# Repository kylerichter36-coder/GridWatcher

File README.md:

# GridWatcher v0.3

> An edge electrical grid telemetry device that monitors AC line fluctuations and predicts power outages 20 to 60 seconds before they happen, sending alerts over 4G LTE cellular. Built for **Hack Club Fallen** (Maker Faire Shenzhen, Dec 2026).

**Author:** Kyle Mason Richter (`@fuelled` on Hack Club Slack / `kylerichter36-coder` on GitHub)  
**Target:** Hack Club Fallen — Maker Faire Shenzhen (Dec 11–14, 2026)  
**Hardware Repo:** [https://github.com/kylerichter36-coder/GridWatcher](https://github.com/kylerichter36-coder/GridWatcher)  
**BOM:** [bom.csv](bom.csv) (Includes links and pricing for every single part)  
**3D CAD Assembly:** [GriDwatcher_china_v0.3.step](Hardware/GridWatcher_v0.3/GriDwatcher_china_v0.3.step)  

---

## Why I Built This

If you live in South Africa like me, you already know the problem: our power grid is completely broken. Between rolling blackouts (load shedding), localized substation cable theft, and sudden breaker trips, our electricity cuts out all the time without any warning. These sudden drops corrupt computers, kill power supplies, and leave households stranded in the dark.

Most commercial energy monitors are totally reactive—they only text you *after* the power is already dead. But power grids dont just vanish instantaneously: before an electrical feeder collapses, the system exhibits measurable micro-fluctuations (sub-hertz frequency jitter, voltage sag gradients, and harmonic noise). 

I built GridWatcher to measure these exact micro-fluctuations and predict outages **20 to 60 seconds before total power failure**, giving you time to save your work, shut down sensitive equipment, or switch over backup systems.

---

## How to Use GridWatcher

GridWatcher is designed to be an autonomous, set-and-forget wall monitor:

1. **Installation & AC Hookup:**  
   Plug the device directly into an AC wall socket (100–240V AC, 50/60Hz) or wire it into your home electrical distribution board. Input power is protected by an on-board 1A slow-blow fuse and 10D471K MOV surge clamp.
2. **Autonomous Startup & 4G Link:**  
   On boot, the isolated Hi-Link 5V power supply turns on the board and starts charging the backup LiPo battery via the BQ24074 PMIC. The SIMCom A7670E modem connects to the local cellular tower over LTE Cat-1. It requires zero Wi-Fi pairing or local router dependencies, so it stays online even when home routers die during grid failures.
3. **Real-Time Monitoring:**  
   The BL0939 IC continuously measures line voltage, current, and frequency. The ESP32-S3 runs the deterministic state classifier and feeds rolling feature buffers into the Random Forest prediction engine.
4. **Early-Warning Outage Prediction:**  
   If the ML engine detects voltage sag slopes or frequency decay jitter indicating grid failure within the upcoming 20–60 seconds, it sends an immediate SMS alert and MQTT warning to your phone so you can save work and protect equipment before the blackout hits.
5. **Blackout Ride-Through & Black-Box Logging:**  
   When mains power drops, the battery circuit takes over with zero drop-out. The device freezes the preceding 60 seconds of high-speed electrical waveform data to the 1GB SD-NAND flash chip for post-incident diagnostics.

---

## 3D CAD Assembly & Physical Design

GridWatcher is designed as a monolithic 2-layer integrated PCBA (113.40 x 69.22 mm) that mounts cleanly inside a 3D-printed snap-fit wall enclosure. Zero loose devboards, zero breadboard jumper wires, and zero external USB ports that collect dust.

*Full 3D CAD STEP mechanical model available at [Hardware/GridWatcher_v0.3/GriDwatcher_china_v0.3.step](Hardware/GridWatcher_v0.3/GriDwatcher_china_v0.3.step).*

---

## How It Works (System Architecture)

```
[230V AC Mains] 
       │
       ├──> [Hi-Link HLK-10M05 5V SMPS] ──> [CLC Pi-Filter] ──> [BQ24074 PMIC] ──> [SY8089 3.3V Buck] ──> [ESP32-S3 Core]
       │                                                              │
       │                                                       [1S LiPo Battery]
       │                                                              │
       ├──> [ZMPT101K Transformer] ──> [BL0939 Dual-Channel Meter] ───┘ (MAX17048 Fuel Gauge)
                                                    │
                                             (UART Telemetry)
                                                    │
                                                    ▼
                                            [ESP32-S3 Compute]
                                                    │
                                   ┌────────────────┴────────────────┐
                                   ▼                                 ▼
                     [Layer 1: Deterministic Rules]    [Layer 2: Random Forest ML]
                     (Blackout / Surge / Sag / Normal) (0-100% Pre-Outage Risk Index)
                                   │                                 │
                                   └────────────────┬────────────────┘
                                                    ▼
                                   [TXS0102 Level Shifter (1.8V <-> 3.3V)]
                                                    │
                                     [SIMCom A7670E 4G LTE Modem]
                                                    │
                                            (MQTT & SMS Alerts)
```

1. **AC Power Delivery & Safety:** Mains electricity (100–240V AC) enters through a 1A slow-blow fuse and 10D471K metal oxide varistor (MOV) for lightning and surge clamping. An isolated Hi-Link HLK-10M05 AC-DC module steps mains down to 5V DC, followed by a CLC Pi-filter (470µF + 10µH + 100µF) to eliminate high-frequency switching ripple.
2. **Precision Metering:** A ZMPT101K potential transformer provides 4kV galvanic isolation between mains and low-voltage logic. The isolated AC wave is sampled by a dedicated Shanghai Belling BL0939 dual-channel energy measurement IC, calculating hardware true RMS voltage, active current, power factor, and line frequency.
3. **Uninterruptible Power Path:** A Texas Instruments BQ24074 PMIC routes system power directly from mains while charging an external 1S Li-ion battery. If mains collapses, it switches system rails to battery power instantaneously with zero drop-out. A Maxim MAX17048 I2C fuel gauge tracks real-time battery percentage.
4. **Compute & Machine Learning:** An ESP32-S3-WROOM-1-N16R8 runs a dual-layer classification engine. Layer 1 executes a deterministic C++ state machine; Layer 2 feeds rolling 10s and 30s feature buffers ($dV/dt$, $dF/dt$, $V_{std}$, $F_{std}$, $V_{slope}$) into an embedded Random Forest decision tree model (`grid_model.h`) to compute pre-outage risk scores (0–100%).
5. **Direct 4G Cellular Link:** When risk exceeds 70% or power drops, a SIMCom A7670E Cat-1 LTE modem transmits telemetry packets over MQTT and dispatches emergency SMS alerts directly to your phone—independent of local Wi-Fi or home routers which die during blackouts!
6. **Black-Box Flash Waveform Storage:** An industrial 1GB SD-NAND flash chip (`XTSDG08GWSIGA`, LGA-8) sits on an SDMMC bus, recording raw high-speed electrical waveforms before and after trip events for post-incident power quality analysis.

---

## Schematic (10 Functional Blocks)

The schematic is organized into 10 modular functional blocks in KiCad 10:

1. **Mains Input & Protection:** Fuse, MOV, Hi-Link 5V SMPS, ZMPT101K potential transformer.
2. **AC Measure:** Shanghai Belling BL0939 dual-channel energy IC with precision 412k voltage divider.
3. **Charger:** TI BQ24074 dynamic power-path manager and 1.0A Li-ion charger.
4. **Program Pins:** 4 gold flush pogo-pin pads (VBUS, GND, D+, D-) with SS14 reverse-power isolation diode.
5. **LDO / Buck:** Silergy SY8089A1AAC 2A 1.5MHz synchronous step-down converter for 3.3V system logic.
6. **Fuel Gauge:** Maxim MAX17048 I2C battery state-of-charge IC.
7. **NAND SD:** XTX 1GB SD-NAND LGA-8 flash chip with 5x 10k pull-ups and 22Ω clock damping resistor (`R22`).
8. **Logic Shifter:** TI TXS0102DCUR bidirectional level translator (1.8V cellular baseband <-> 3.3V MCU).
9. **MOSFETs:** Dual onsemi BSS138 N-channel FET switches for modem PWRKEY and RESET lines.
10. **Cellular Modem:** SIMCom A7670E 4G LTE Cat-1 baseband, hinged Nano-SIM socket, and 470µF tantalum buffer.

---

## PCB Layout & Routing

The PCB was designed and routed in KiCad as a 2-layer FR-4 board measuring **113.40 x 69.22 mm**:

### Key Layout Considerations:
* **High-Voltage Creepage & Clearance:** 230V AC Live and Neutral copper traces are routed with >3.5 mm physical separation and routed away from all 3.3V digital signals.
* **RF Keep-Out Zone:** An etched copper trace antenna sits on the top edge with zero copper planes underneath (hatched keep-out area) to maintain 50Ω impedance matching.
* **Transient GSM Decoupling:** A 470µF low-ESR tantalum capacitor (`C19`) sits directly beside the A7670E VBAT pins to supply 2.0A transmission burst pulses without triggering undervoltage lockouts.
* **High-Frequency Bypass Placement:** 100nF ceramic decoupling caps sit directly adjacent to ESP32 VDD pins and SD-NAND VCC pins, tied into the bottom ground plane with dedicated vias.

---

## Subsystem Pinout & Interconnect Mapping

| ESP32-S3 Pin | Signal Net | Connected Peripheral | Function |
| :--- | :--- | :--- | :--- |
| **GPIO19 (U0RXD)** | `/RX 939` | Shanghai Belling BL0939 TX | Reads true RMS voltage, current, and line frequency |
| **GPIO20 (U0TXD)** | `/TX 939` | Shanghai Belling BL0939 RX | Configures calibration registers and measurement modes |
| **GPIO15** | `/esp32 gpio` | BL0939 CF1 Output | High-speed electrical pulse / energy interrupt |
| **GPIO10** | `/MODEM_TX_3V3` | TI TXS0102 Port A1 | Level-shifted UART TX to SIMCom A7670E (1.8V domain) |
| **GPIO11** | `/MODEM_RX_3V3` | TI TXS0102 Port A8 | Level-shifted UART RX from SIMCom A7670E (1.8V domain) |
| **GPIO9** | `/ESP_PWRKEY` | onsemi BSS138 Q1 Gate | Active-low modem power key pulse control |
| **GPIO8** | `/ESP_RESET` | onsemi BSS138 Q2 Gate | Active-low modem hardware reset control |
| **GPIO11, 12, 13, 14** | `/IO11`..`/IO14` | XTX 1GB SD-NAND LGA-8 | 1-bit SDMMC bus (CMD, CLK via 22Ω R22, DAT0, CS) |
| **GPIO6 (SDA)** | `/ESP SDA` | Maxim MAX17048 SDA | I2C battery fuel gauge data (pulled up to 3.3V) |
| **GPIO7 (SCL)** | `/ESP SCL` | Maxim MAX17048 SCL | I2C battery fuel gauge clock (pulled up to 3.3V) |
| **GPIO4** | `/ESP GPIO CHG` | TI BQ24074 CHG Pin | Open-drain battery charging status monitoring |
| **GPIO5** | `/ESP GPIO-` | Status LED Indicator | Visual operational state / warning blinker |
| **USB D+ / D-** | `USB_D+` / `USB_D-` | Flush Pogo Test Pads | Native ESP32-S3 ROM bootloader programming jig |

---

## Bill of Materials (BOM)

The complete Bill of Materials with supplier links and prices is available in [bom.csv](bom.csv).

### Summary Breakdown:

| Category | Description | Sourcing | Cost (USD) | Cost (ZAR) |
| :--- | :--- | :--- | :---: | :---: |
| **JLCPCB SMT Order** | 2 Assembled PCBAs (Top SMT) + 5 Bare 2-Layer PCBs + Courier Delivery | JLCPCB | $327.85 | R 5,901.30 |
| **Micro Robotics Order** | Hi-Link 10W SMPS (x2), 275V Varistors (x2 pk), 1A Glass Fuses, RAM Delivery | Micro Robotics SA | $20.40 | R 366.85 |
| **LCSC Consolidated** | ZMPT101B Transformers (x2), 5x20mm PCB Clips (x4), JST Header (x2) | LCSC (Combined) | $3.43 | R 61.74 |
| **Diagnostic Tool** | FNIRSI DSO153 Pocket Mini-Oscilloscope (Takealot SA) | Takealot | $65.30 | R 1,175.00 |
| **Self-Owned ($0)** | 1S 3.7V Li-ion battery, 3D printed enclosure, pogo jig, soldering tools | Reused | $0.00 | R 0.00 |
| **Total Project Funding** | **Hack Club Grant Funding Request** | **HCB Card** | **$416.98** | **R 7,504.89** |

*(Calculated at 1 USD = ~18.00 ZAR based on official supplier receipts and quotes)*

---

## Firmware Architecture & Driver Skeleton

Because the physical boards are currently in manufacturing at JLCPCB, I obviously cannot flash or debug low-level hardware registers until the physical PCBAs arrive on my desk! 

However, the complete firmware architecture and FreeRTOS task structure is already implemented in [firmware/firmware.ino](firmware/firmware.ino):

```
firmware/
├── firmware.ino          # Modular FreeRTOS driver architecture & task scheduler
├── grid_model.h          # Exported Random Forest C++ decision tree ensemble
└── secrets.h.example     # Network configuration template
```

### FreeRTOS Modular Tasks:
1. `Task_EnergyMetering`: UART driver reading registers from the Shanghai Belling BL0939 (Voltage RMS, Current RMS, Frequency).
2. `Task_PredictionEngine`: Evaluates instantaneous Layer 1 rules and computes rolling rates of change ($dV/dt$, $dF/dt$, $V_{std}$) feeding `grid_model.h` to generate pre-outage risk scores (0–100%).
3. `Task_CellularTelemetry`: Controls the SIMCom A7670E via AT commands over level-shifted UART, publishing periodic MQTT telemetry and dispatching emergency SMS alerts during predicted grid failure.
4. `Task_BlackboxStorage`: SDMMC driver writing continuous high-speed waveform data buffers to the 1GB SD-NAND flash chip.
5. `Task_PowerManagement`: Polls the MAX17048 fuel gauge over I2C and monitors the BQ24074 `CHG` status pin.

---

## Repository Structure

```
GridWatcher/
├── Hardware/
│   └── GridWatcher_v0.3/             # Bespoke monolithic PCBA design files
│       ├── GriDwatcher china.kicad_pcb  # KiCad PCB layout (113.40 x 69.22 mm)
│       ├── GriDwatcher china.kicad_sch  # Complete 10-block schematic
│       ├── GriDwatcher china.kicad_pro  # KiCad project definition
│       ├── GriDwatcher china.kicad_prl  # KiCad local settings
│       ├── GriDwatcher_china_gerbers.zip# RS-274X manufacturing Gerbers & drill files
│       ├── GriDwatcher_china_v0.3.step  # 3D mechanical CAD assembly model
│       ├── jlcpcb_bom.csv            # Pick-and-place BOM for JLCPCB
│       ├── jlcpcb_cpl.csv            # Pick-and-place centroid coordinate file
│       └── bom.csv                   # Comprehensive BOM with parts links
├── docs/                             # Project screenshots & visual assets
│   ├── 3d_cad_assembly.png           # 3D CAD mechanical render
│   ├── pcb_render_top.jpg            # 3D top board render with Hack Club silkscreen
│   ├── pcb_routing.png               # KiCad 2-layer routing with dimensions
│   └── schematic_10blocks.png        # Complete 10-block functional schematic
├── firmware/                         # Microcontroller firmware skeleton & ML model
│   ├── firmware.ino                  # FreeRTOS driver structure & task scheduler
│   ├── grid_model.h                  # Compiled Random Forest decision trees
│   └── secrets.h.example             # Credential configuration template
├── windows_trainer/                  # Python machine learning retraining pipeline
│   ├── gridwatcher_ml_gui.py         # Rolling feature extraction & C++ exporter
│   └── simulate_ml_brain.py          # Synthetic grid failure training simulation
├── bom.csv                           # Root BOM with links and pricing for every item
├── JOURNAL.md                        # Detailed engineering build log & session notes
└── README.md
```

---

## Next Steps for Build Submission

1. **Receive Manufactured PCBAs:** Receive assembled boards from JLCPCB.
2. **Hand Solder Through-Hole Components:** Solder Hi-Link SMPS, ZMPT101K transformer, MOV, fuse holder, and JST battery connector.
3. **Probe & Verify with Oscilloscope:** Scope the ZMPT101K transformer secondary winding to verify safe AC amplitude scaling, check SD-NAND clock damping, and observe buck switching stability under 2A cellular pulses.
4. **Tune Low-Level Registers:** Finalize BL0939 UART register offsets and calibrate against a reference multimeter.
5. **3D Print Enclosure & Field Deploy:** Snap board into the 3D-printed case, mount next to the household distribution board, and record live grid telemetry for the Shenzhen demo!

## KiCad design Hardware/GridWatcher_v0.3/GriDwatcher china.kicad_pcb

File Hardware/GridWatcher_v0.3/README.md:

# GridWatcher Hardware v0.3

Monolithic 2-layer integrated telemetry and energy monitoring board designed for JLCPCB SMT assembly, replacing the modular v0.2 breakout carrier board.

## Specifications

* **Board Dimensions:** 113.40 mm x 69.22 mm (2-layer FR-4, 1.6 mm thickness, 1 oz copper)
* **Microcontroller:** ESP32-S3-WROOM-1-N16R8 (16MB Flash, 8MB Octal PSRAM, 2.4 GHz Wi-Fi + BLE 5)
* **Cellular Modem:** SIMCom A7670E LTE Cat-1 LGA module with micro-strip trace to test point / external antenna, paired with a hinged 6-pin Nano-SIM socket (J2)
* **Energy Metering:** BL0939 dual-channel energy measurement IC (UART interface to ESP32-S3) + ZMPT101K voltage transformer + dual 412k 1206 voltage divider string
* **Battery & Power Path:**
  * Hi-Link HLK-10M05 isolated 10W (5V 2A) AC-DC converter for direct 100-240V AC mains operation
  * TI BQ24074 1.5A Li-ion linear charger with autonomous dynamic power-path management (SYS output prioritized over battery charging)
  * Silergy SY8089A1AAC 2A synchronous step-down buck converter (5V/VSYS -> 3.3V system rail)
  * Maxim MAX17048 I2C fuel gauge (DFN-8) for 1S battery state-of-charge tracking
* **Non-Volatile Storage:** XTX XTSDG08GWSIGA 1GB (8Gb) SD-NAND in LGA-8 package (SDIO 1-bit / 4-bit bus) for continuous electrical event recording
* **Level Translation:** TI TXS0102DCUR bidirectional voltage translator bridging 3.3V ESP32 UART logic to 1.8V A7670E cellular baseband UART

## Subsystem Pin Mapping

| ESP32-S3 Pin | Function / Net | Connected Peripheral |
| :--- | :--- | :--- |
| GPIO4 | `/ESP GPIO CHG` | BQ24074 `CHG` open-drain status |
| GPIO5 | `/ESP GPIO-` | Status LED / auxiliary GPIO |
| GPIO6 | `/ESP SDA` | MAX17048 I2C data (pulled up to 3.3V via R10) |
| GPIO7 | `/ESP SCL` | MAX17048 I2C clock (pulled up to 3.3V via R11) |
| GPIO8 | `/ESP_RESET` | A7670E `RESET` gate driver (via N-channel FET Q2) |
| GPIO9 | `/ESP_PWRKEY` | A7670E `PWRKEY` gate driver (via N-channel FET Q1) |
| GPIO10 | `/MODEM_TX_3V3` | TXS0102 Port A pin 1 (level-shifted from A7670E TXD 1.8V) |
| GPIO11 | `/MODEM_RX_3V3` | TXS0102 Port A pin 8 (level-shifted to A7670E RXD 1.8V) |
| GPIO10, 11, 12, 13 | `/IO10`, `/IO11`, `/IO12`, `/IO13` | XTX SD-NAND LGA-8 (DAT2, DAT3, CLK, CMD lines) |
| GPIO15 | `/esp32 gpio` | BL0939 CF1 / interrupt pulse output |
| GPIO19 (U0RXD) | `/RX 939` | BL0939 UART TX output (3.3V domain) |
| GPIO20 (U0TXD) | `/TX 939` | BL0939 UART RX input (3.3V domain) |
| USB D- / D+ | Direct pads | Native ESP32-S3 USB interface |

## JLCPCB SMT Production Files

All production outputs are located in this directory:

* `GriDwatcher_china_gerbers.zip`: Standard RS-274X Gerbers and Excellon drill files generated from KiCad 8. Silkscreen contains hidden `JLCJLCJLCJLC` order marker under U1 footprint.
* `jlcpcb_bom.csv`: SMT pick-and-place Bill of Materials with verified LCSC part codes.
* `jlcpcb_bom_complete.csv`: Full project BOM including hand-soldered through-hole components.
* `jlcpcb_cpl.csv`: Centroid placement file with component rotations mapped for JLCPCB automated feeders.
* `GriDwatcher_china_v0.3.step`: Complete 3D mechanical assembly model (OpenCASCADE AP214 format).

### Component Sourcing & Errata

1. **Through-Hole Parts (Manual Post-Assembly):**
   * `U1`: Hi-Link HLK-10M05 isolated AC-DC module (Micro Robotics SA)
   * `TR1`: ZMPT101B / ZMPT101K precision 2mA:2mA voltage transformer (LCSC C111858)
   * `RV1`: 275VAC metal oxide varistor (Micro Robotics 5D431 / 10D471K)
   * `F1`: 5x20 mm PCB fuse clips (LCSC C3130) + 1A glass cartridge fuse (Micro Robotics FUSE20-1A)
   * `J1`: JST-PH 2.0 mm right-angle 2-pin battery connector (LCSC C131337)
2. **SMT Pick-and-Place Feeder Codes:**
   * `Q1, Q2`: SOT-23 N-channel MOSFETs (`C52895` onsemi BSS138).
   * `J2`: Hinged Nano-SIM 6-pin socket (`C2963104` BOOMELE NANO SIM 6PIN).
   * `L1`: 10uH shielded power inductor 7.3x7.3 mm (`C915310` MetalLions MSRH74-100MT).
   * `C19`: 470uF 6.3V Case D 7343 low-ESR tantalum capacitor (`C7229`).
   * `U4`: SOT-23-5 buck regulator requires 180° rotation offset in CPL relative to KiCad standard orientation.
   * `C2`: 100uF 25V 6.3x7.7 mm SMD aluminum electrolytic requires 0° CPL orientation to align cathode with GND pad.
3. **Do Not Populate (DNP):**
   * `C24`, `C25`: RF tuning pads near SIM socket reserved for impedance matching on custom antenna geometries.

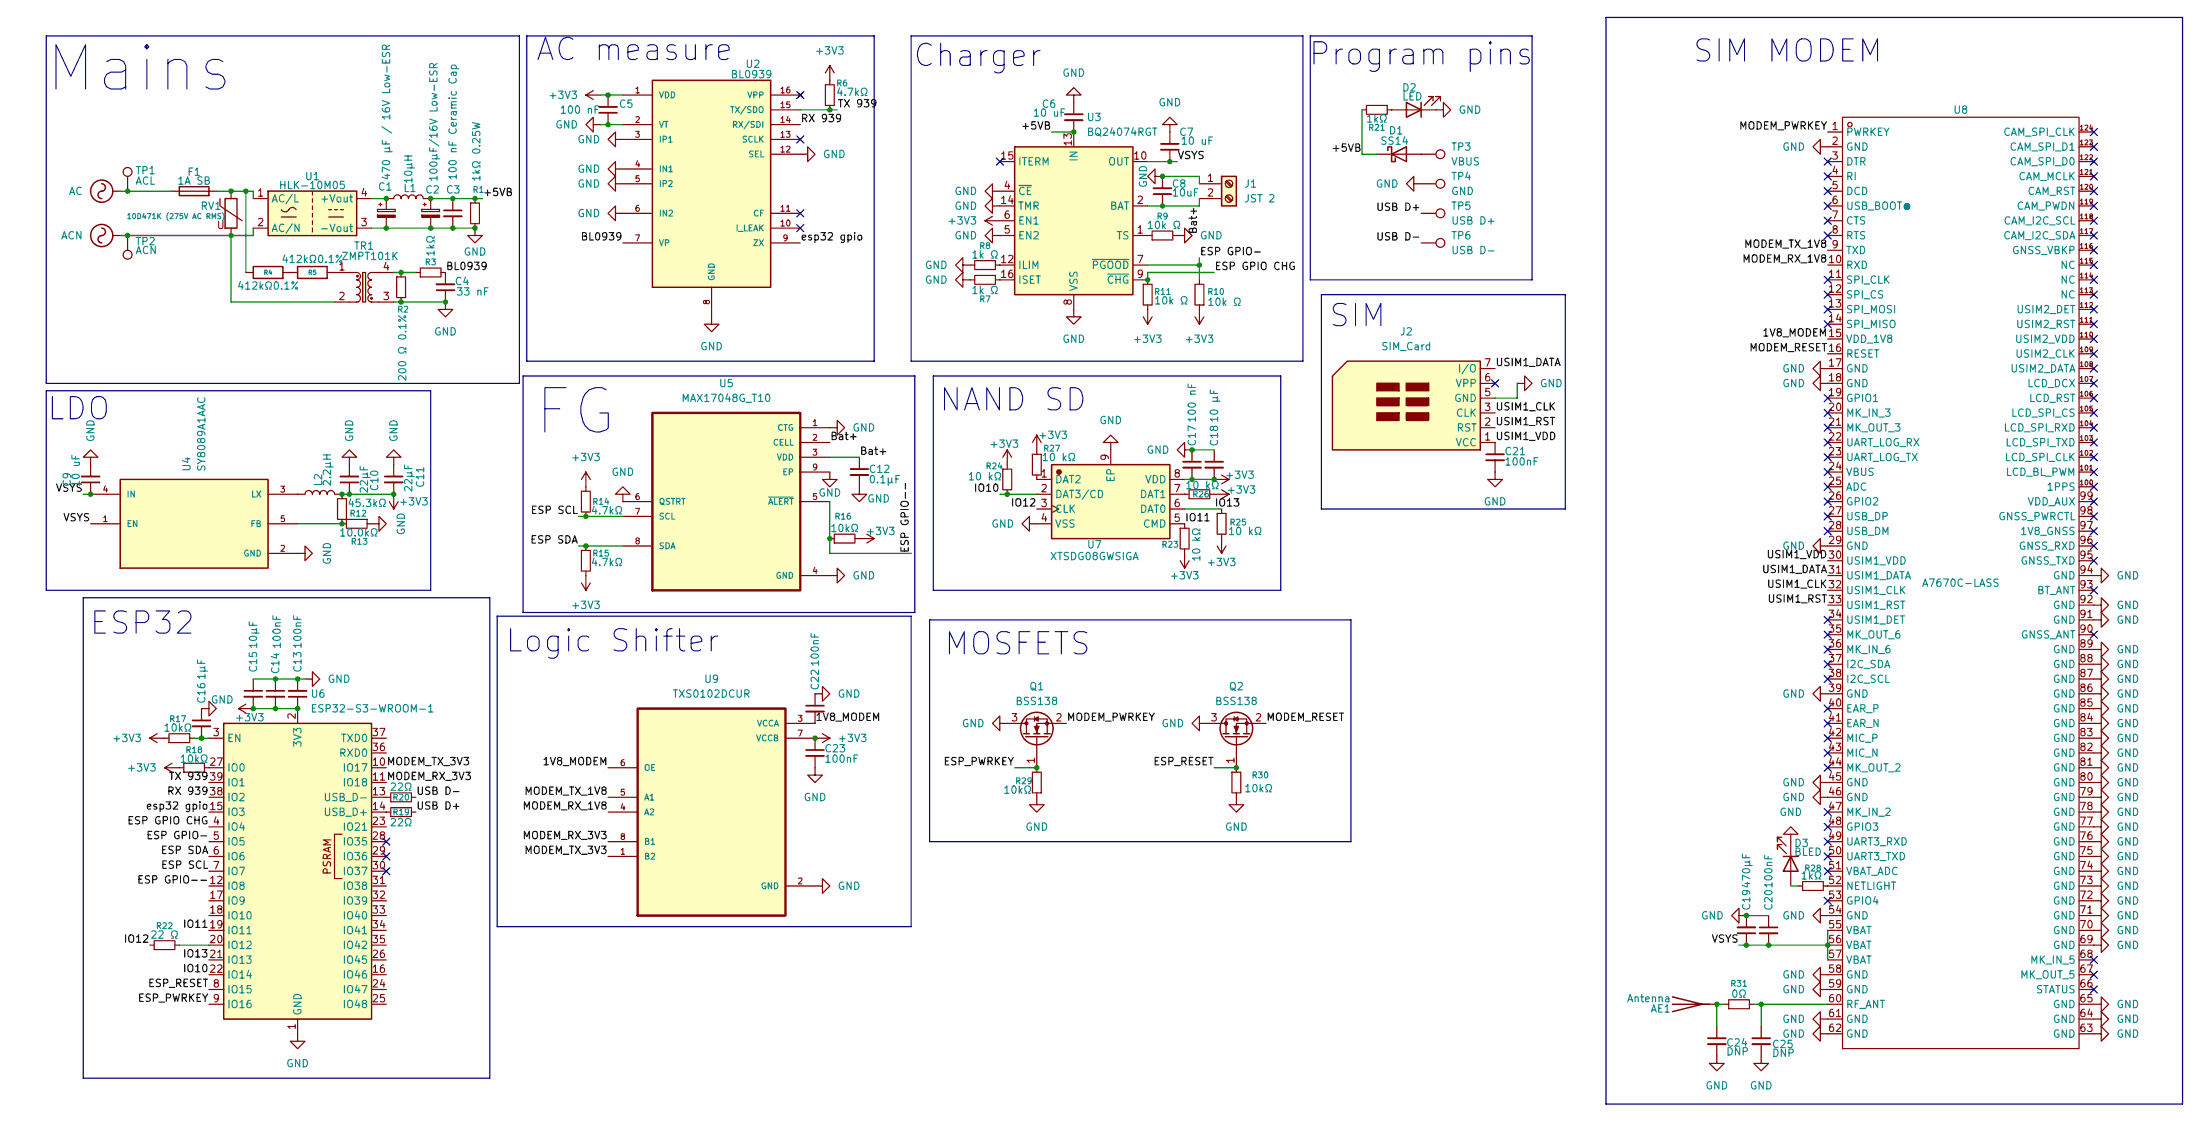
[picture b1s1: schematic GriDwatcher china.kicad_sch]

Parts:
AE1: Antenna; TestPoint_Pad_D1.5mm
C1: 470 µF / 16V Low-ESR; CP_Elec_8x10.5
C2: 100μF/16V Low-ESR; CP_Elec_6.3x7.7
C3: 100 nF Ceramic Cap; C_0603_1608Metric
C4: 33 nF; C_0603_1608Metric
C5, C17: 100 nF; C_0603_1608Metric
C6, C7, C9: 10 uF; C_0805_2012Metric
C8: 10uF; C_0805_2012Metric
C10, C11: 22μF; C_0805_2012Metric
C12: 0.1μF; C_0603_1608Metric
C13, C14, C20, C21, C22, C23: 100nF; C_0603_1608Metric
C15: 10μF; C_0805_2012Metric
C16: 1μF; C_0603_1608Metric
C18: 10 µF; C_0805_2012Metric
C19: 470μF; CP_EIA-7343-31_Kemet-D
C24, C25: DNP; C_0603_1608Metric
D1: SS14; D_SMA
D2: LED; LED_0805_2012Metric
D3: BLED; LED_0805_2012Metric
F1: 1A SB; Fuseholder_Clip-5x20mm_Eaton_1A5601-01_Inline_P20.80x6.76mm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
J1: JST 2; JST_PH_S2B-PH-K_1x02_P2.00mm_Horizontal
J2: SIM_Card; nanoSIM_GCT_SIM8060-6-0-14-00
L1: 10μH; L_7.3x7.3_H4.5
L2: 2.2μH; L_Bourns-SRN4018
Q1, Q2: BSS138; SOT-23
R1: 1kΩ 0.25W; R_0805_2012Metric
R2: 200 Ω 0.1%; R_0805_2012Metric
R3, R21, R28: 1kΩ; R_0603_1608Metric
R4, R5: 412kΩ0.1%; R_1206_3216Metric
R6, R14, R15: 4.7kΩ; R_0603_1608Metric
R7, R8: 1k Ω; R_0603_1608Metric
R9, R10, R11: 10k Ω; R_0603_1608Metric
R12: 45.3kΩ; R_0603_1608Metric
R13: 10.0kΩ; R_0603_1608Metric
R16, R17, R18, R29, R30: 10kΩ; R_0603_1608Metric
R19, R20: 22Ω; R_0603_1608Metric
R22: 22 Ω; R_0603_1608Metric
R23, R24, R25, R26, R27: 10 kΩ; R_0603_1608Metric
R31: 0Ω; R_0603_1608Metric
RV1: 10D471K (275V AC RMS); RV_Disc_D12mm_W4.3mm_P7.5mm
TP1: ACL; TestPoint_THTPad_D2.5mm_Drill1.2mm
TP2: ACN; TestPoint_THTPad_D2.5mm_Drill1.2mm
TP3: VBUS; TestPoint_Pad_D2.0mm
TP4: GND; TestPoint_Pad_D2.0mm
TP5: USB D+; TestPoint_Pad_D2.0mm
TP6: USB D-; TestPoint_Pad_D2.0mm
TR1: ZMPT101K; Transformer_Zeming_ZMPT101K
U1: HLK-10M05; Converter_ACDC_Hi-Link_HLK-10Mxx
U2: BL0939; SOIC127P610X180-16N
U3: BQ24074RGT; VQFN-16-1EP_3x3mm_P0.5mm_EP1.6x1.6mm
U4: SY8089A1AAC; SOT95P285X130-5N; PARTREV 0.0
U5: MAX17048G_T10; SON50P200X200X80-9N
U6: ESP32-S3-WROOM-1
U7: XTSDG08GWSIGA; XTX_SDNAND_LGA-8-EP_6x8mm_P1.27mm; MPN XTSDG08GWSIGA; LCSC C25836657
U8: A7670C-LASS; A7670E; Manufacturer Part A7670E-LASE; LCSC Part Name A7670E-LASE
U9: TXS0102DCUR; SOP50P310X90-8N

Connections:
+3V3: C5.2, C10.1, C11.2, C13.1, C14.2, C15.2, C17.2, C18.2, C23.1, L2.2, R6.1, R10.1, R11.2, R12.2, R14.1, R15.2, R16.2, R17.1, R18.1, R23.2, R24.1, R25.2, R26.2, R27.1, U2.1 (VDD), U3.6 (EN1), U6.2 (3V3), U7.8 (VDD), U9.7 (VCCB)
/1V8_MODEM: C22.2, U8.15 (VDD_1V8), U9.3 (VCCA), U9.6 (OE)
/+5VB: C2.1, C3.1, C6.2, D1.1 (K), L1.2, R1.1, R21.2, U3.13 (IN)
/BL0939: C4.2, R3.2, U2.7 (VP)
/Bat+: C8.1, C12.1, J1.2, U3.2 (BAT), U3.3 (BAT), U5.2 (CELL), U5.3 (VDD)
/ESP GPIO CHG: R11.1, U3.9 (~CHG), U6.4 (IO4)
/ESP GPIO-: R10.2, U3.7 (~PGOOD), U6.5 (IO5)
/ESP GPIO--: R16.1, U5.5 (~ALERT), U6.12 (IO8)
/ESP SCL: R14.2, U5.7 (SCL), U6.7 (IO7)
/ESP SDA: R15.1, U5.8 (SDA), U6.6 (IO6)
/ESP_PWRKEY: Q1.1 (G), R29.2, U6.9 (IO16)
/ESP_RESET: Q2.1 (G), R30.1, U6.8 (IO15)
/IO10: R24.2, U6.22 (IO14), U7.2 (DAT3/CD)
/IO11: R23.1, U6.19 (IO11), U7.5 (CMD)
/IO12: R22.1, U7.3 (CLK)
/IO13: R25.1, U6.21 (IO13), U7.6 (DAT0)
/MODEM_PWRKEY: Q1.2 (S), U8.1 (PWRKEY)
/MODEM_RESET: Q2.2 (S), U8.16 (RESET)
/MODEM_RX_1V8: U8.10 (RXD), U9.4 (A2)
/MODEM_RX_3V3: U6.11 (IO18), U9.8 (B1)
/MODEM_TX_1V8: U8.9 (TXD), U9.5 (A1)
/MODEM_TX_3V3: U6.10 (IO17), U9.1 (B2)
/RX 939: U2.14 (RX/SDI), U6.38 (IO2)
/TX 939: R6.2, U2.15 (TX/SDO), U6.39 (IO1)
/USB D+: R19.2, TP5.1 (1_1)
/USB D-: R20.2, TP6.1 (1_1)
/USIM1_CLK: J2.3 (CLK), U8.32 (USIM1_CLK)
/USIM1_DATA: J2.7 (I/O), U8.31 (USIM1_DATA)
/USIM1_RST: J2.2 (RST), U8.33 (USIM1_RST)
/USIM1_VDD: C21.1, J2.1 (VCC), U8.30 (USIM1_VDD)
/VSYS: C7.2, C9.1, C19.1, C20.2, U3.10 (OUT), U3.11 (OUT), U4.1 (EN), U4.4 (IN), U8.55 (VBAT), U8.56 (VBAT), U8.57 (VBAT)
/esp32 gpio: U2.9 (ZX), U6.15 (IO3)
AC: F1.1, TP1.1 (1_1)
ACN: RV1.2, TP2.1 (1_1), TR1.2, U1.2 (AC/N)
GND: C1.2, C2.2, C3.2, C4.1, C5.1, C6.1, C7.1, C8.2, C9.2, C10.2, C11.1, C12.2, C13.2, C14.1, C15.1, C16.1, C17.1, C18.1, C19.2, C20.1, C21.2, C22.1, C23.2, C24.2, C25.2, D2.1 (K), D3.1 (K), J1.1, J2.5 (GND), Q1.3 (D), Q2.3 (D), R1.2, R2.2, R7.2, R8.2, R9.2, R13.1, R29.1, R30.2, TP4.1 (1_1), TR1.3, U1.3 (-Vout), U2.2 (VT), U2.3 (IP1), U2.4 (IN1), U2.5 (IP2), U2.6 (IN2), U2.8 (GND), U2.12 (SEL), U3.4 (~CE), U3.5 (EN2), U3.8 (VSS), U3.14 (TMR), U3.17 (VSS), U4.2 (GND), U5.1 (CTG), U5.4 (GND), U5.6 (QSTRT), U5.9 (EP), U6.1 (GND), U6.40 (GND), U6.41 (GND), U7.4 (VSS), U7.9 (EP), U8.2 (GND), U8.17 (GND), U8.18 (GND), U8.29 (GND), U8.39 (GND), U8.45 (GND), U8.46 (GND), U8.54 (GND), U8.58 (GND), U8.59 (GND), U8.61 (GND), U8.62 (GND), U8.63 (GND), U8.64 (GND), U8.65 (GND), U8.69 (GND), U8.70 (GND), U8.71 (GND), U8.72 (GND), U8.73 (GND), U8.74 (GND), U8.75 (GND), U8.76 (GND), U8.77 (GND), U8.78 (GND), U8.79 (GND), U8.80 (GND), U8.81 (GND), U8.82 (GND), U8.83 (GND), U8.84 (GND), U8.85 (GND), U8.86 (GND), U8.87 (GND), U8.88 (GND), U8.89 (GND), U8.91 (GND), U8.92 (GND), U8.94 (GND), U9.2 (GND)
unnamed: AE1.1 (A_1), C24.1, R31.1
unnamed: D1.2 (A), TP3.1 (1_1)
unnamed: D2.2 (A), R21.1
unnamed: D3.2 (A), R28.1
unnamed: R2.1, R3.1, TR1.4
unnamed: R4.2, R5.1
unnamed: R5.2, TR1.1
unnamed: C1.1, L1.1, U1.4 (+Vout)
unnamed: F1.2, R4.1, RV1.1, U1.1 (AC/L)
unnamed: R8.1, U3.12 (ILIM)
unnamed: R7.1, U3.16 (ISET)
unnamed: R9.1, U3.1 (TS)
unnamed: R12.1, R13.2, U4.5 (FB)
unnamed: L2.1, U4.3 (LX)
unnamed: C16.2, R17.2, U6.3 (EN)
unnamed: R18.2, U6.27 (IO0)
unnamed: R22.2, U6.20 (IO12)
unnamed: R19.1, U6.14 (USB_D+)
unnamed: R20.1, U6.13 (USB_D-)
unnamed: R26.1, U7.7 (DAT1)
unnamed: R27.2, U7.1 (DAT2)
unnamed: R28.2, U8.52 (NETLIGHT)
unnamed: C25.1, R31.2, U8.60 (RF_ANT)

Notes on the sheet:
Logic Shifter
MOSFETS
SIM
NAND SD
Mains
SIM MODEM
AC measure
ESP32
LDO
Charger
Program pins

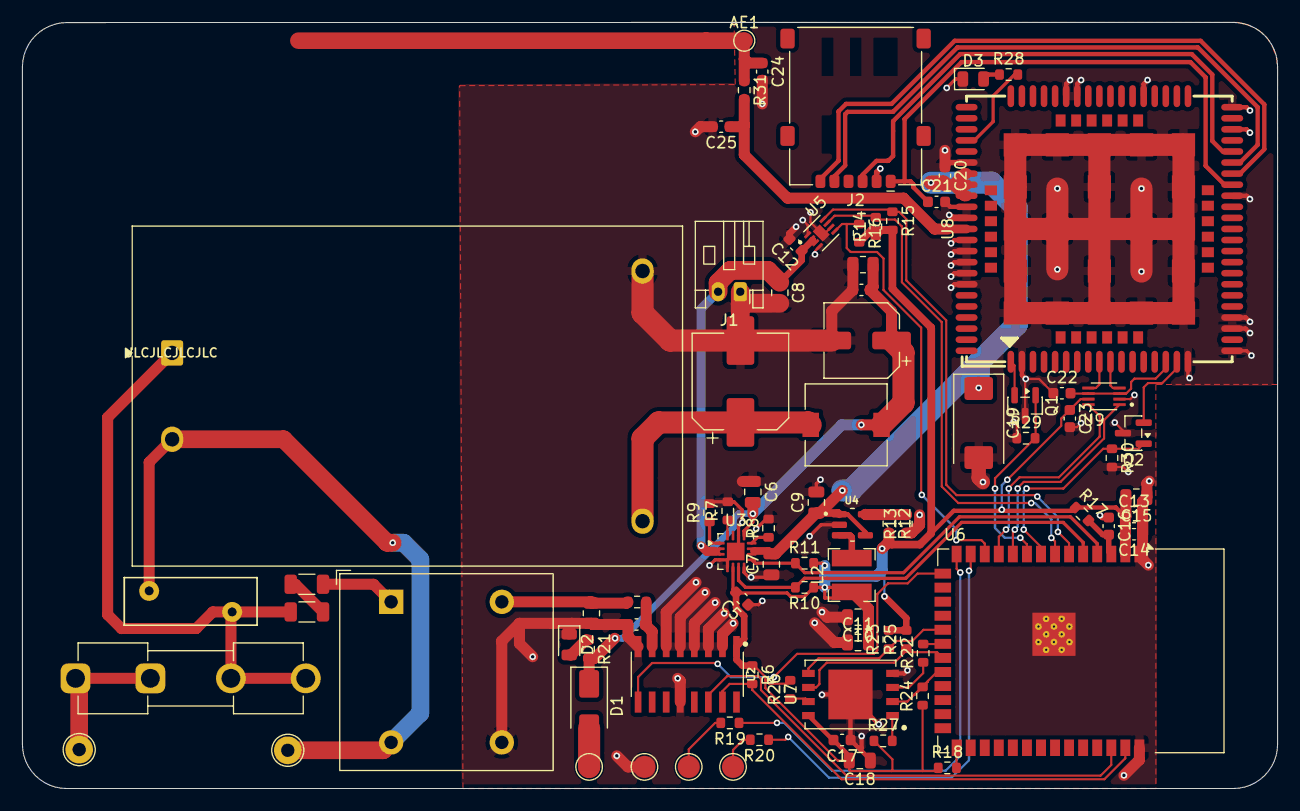
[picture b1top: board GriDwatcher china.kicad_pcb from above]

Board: 2 copper layers, 113.4 x 69.2 mm, 84 parts (0 on the bottom side), 58 nets.

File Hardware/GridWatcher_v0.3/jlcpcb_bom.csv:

Comment,Designator,Footprint,LCSC Part #
470uF 16V SMD Electrolytic 8x10.5mm,C1,CP_Elec_8x10.5,C3341
100uF 16V SMD Electrolytic 6.3x7.7mm,C2,CP_Elec_6.3x7.7,C3338
100nF 50V 0603 X7R Ceramic,"C3, C5, C12, C13, C14, C17, C20, C21, C22, C23",C_0603_1608Metric,C14663
33nF 50V 0603 X7R Ceramic,C4,C_0603_1608Metric,C1613
10uF 25V 0805 X5R Ceramic,"C6, C7, C8, C9, C15, C18",C_0805_2012Metric,C15850
22uF 16V 0805 X5R Ceramic,"C10, C11",C_0805_2012Metric,C45783
1uF 25V 0603 X7R Ceramic,C16,C_0603_1608Metric,C15849
470uF 6.3V Tantalum Case D 7343 Low-ESR,C19,CP_EIA-7343-31_Kemet-D,C7229
SS14 40V 1A Schottky Diode SMA,D1,D_SMA,C2480
LED 0805 Green,D2,LED_0805_2012Metric,C2297
LED 0805 Blue (NETLIGHT),D3,LED_0805_2012Metric,C2296
Nano-SIM Card Socket Push-Pull 6-Pin SMD,J2,nanoSIM_GCT_SIM8060-6-0-14-00,C2963104
10uH Shielded Power Inductor SMD 7.3x7.3mm,L1,L_7.3x7.3_H4.5,C16719
2.2uH Shielded Power Inductor SMD 4018,L2,L_Bourns-SRN4018,C514088
BSS138 N-Channel 50V 0.22A SOT-23,"Q1, Q2",SOT-23,C52895
1k 0805 1% Resistor,R1,R_0805_2012Metric,C17513
200 0805 0.1% Precision Resistor,R2,R_0805_2012Metric,C17540
1k 0603 1% Resistor,"R3, R7, R8, R21, R28",R_0603_1608Metric,C21190
412k 1206 0.1% High-Voltage Precision Resistor,"R4, R5",R_1206_3216Metric,C871304
4.7k 0603 1% Resistor,"R6, R14, R15",R_0603_1608Metric,C25900
10k 0603 1% Resistor,"R9, R10, R11, R13, R16, R17, R18, R23, R24, R25, R26, R27, R29, R30",R_0603_1608Metric,C25804
45.3k 0603 1% Resistor,R12,R_0603_1608Metric,C23080
22 0603 1% Resistor,"R19, R20, R22",R_0603_1608Metric,C23345
0 0603 Link Resistor,R31,R_0603_1608Metric,C21189
BL0939 Dual-Channel Energy Metering IC SOP-16,U2,BL0939:SOIC127P610X180-16N,C2836697
BQ24074RGTR 1.5A Li-Ion Charger & Power-Path VQFN-16,U3,VQFN-16-1EP_3x3mm_P0.5mm_EP1.6x1.6mm,C54313
SY8089A1AAC 2A Synchronous Step-Down Buck SOT-23-5,U4,SY8089A1AAC:SOT95P285X130-5N,C479074
MAX17048G+T10 Li-Ion Fuel Gauge DFN-8,U5,MAX17048G_T10:SON50P200X200X80-9N,C2682616
ESP32-S3-WROOM-1-N16R8 Wi-Fi & BLE Module,U6,ESP32-S3-WROOM-1,C2913202
XTX 1GB SD-NAND LGA-8-EP (XTSDG08GWSIGA),U7,GridWatcher:XTX_SDNAND_LGA-8-EP_6x8mm_P1.27mm,C25836657
SIMCom A7670E-FASE LTE Cat-1 LGA Module,U8,A7670E:A7670E,C7435296
TXS0102DCUR 2-Bit Bidirectional Voltage Translator VSSOP-8,U9,TXS0102DCUR:SOP50P310X90-8N,C53434

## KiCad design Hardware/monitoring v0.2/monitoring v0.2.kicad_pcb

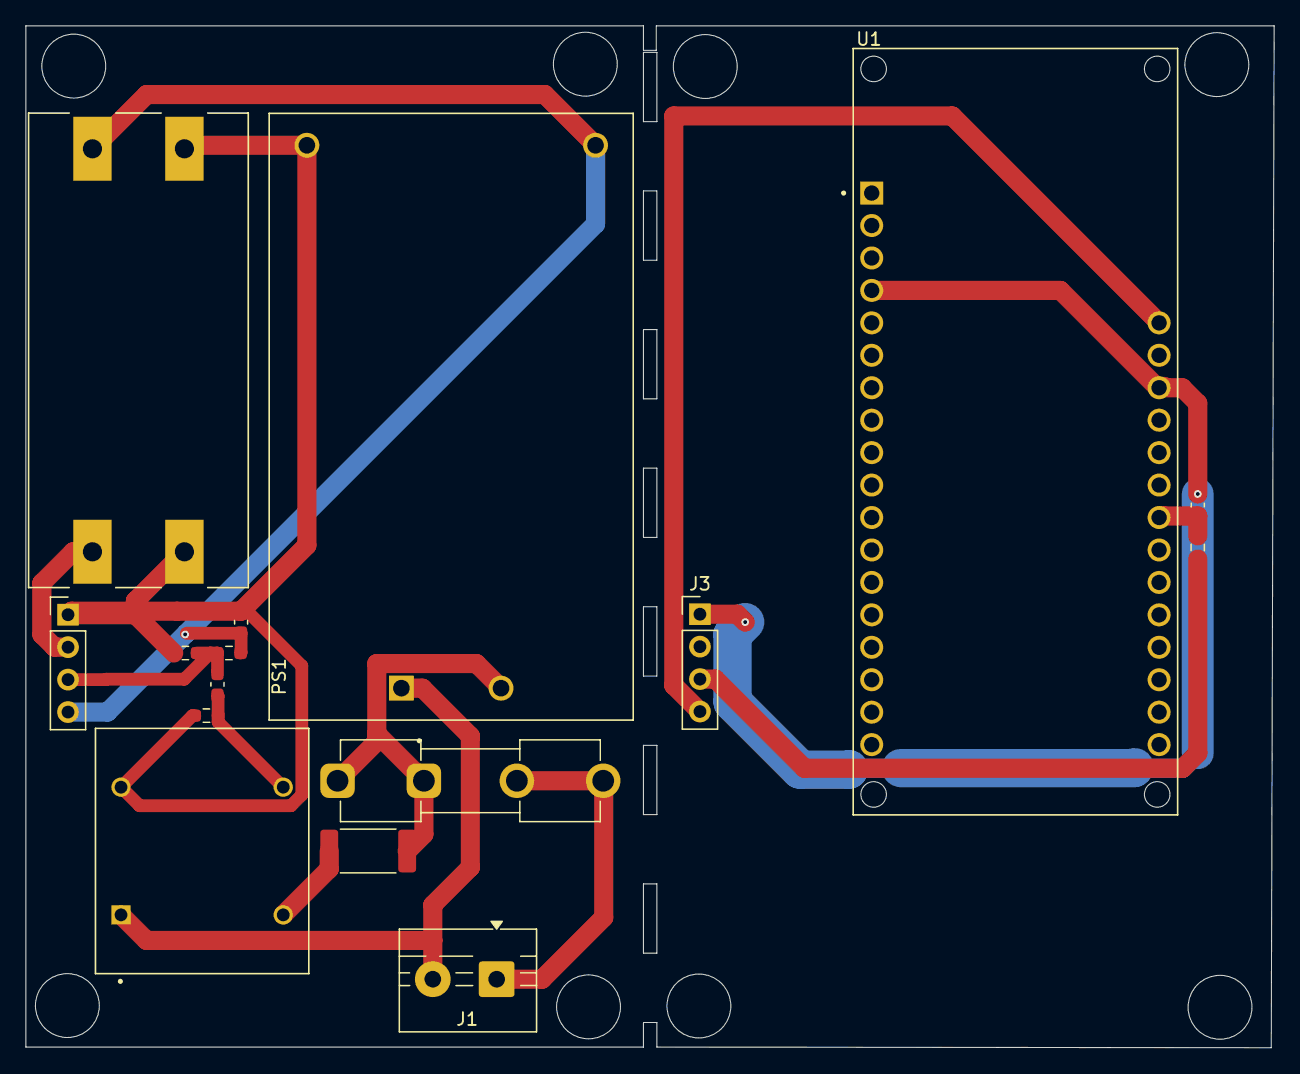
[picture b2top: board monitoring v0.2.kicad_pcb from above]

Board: 2 copper layers, 97.7 x 80.0 mm, 16 parts (0 on the bottom side), 11 nets.

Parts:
C1: 1uF; C_0603_1608Metric_Pad1.08x0.95mm_HandSolder
C2: 0.1uF; C_0603_1608Metric_Pad1.08x0.95mm_HandSolder
C3: 10nF; C_0603_1608Metric_Pad1.08x0.95mm_HandSolder
F1: 1A; Fuseholder_Clip-5x20mm_Eaton_1A5601-01_Inline_P20.80x6.76mm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
J1: ST01x02; TerminalBlock_MaiXu_MX126-5.0-02P_1x02_P5.00mm
J2, J3: Conn_01x04_Pin; PinHeader_1x04_P2.54mm_Vertical
PS1: HLK-10M05; CONV_HLK-10M05
R1: 820K; R_2512_6332Metric_Pad1.40x3.35mm_HandSolder
R2: |2k; R_0603_1608Metric_Pad0.98x0.95mm_HandSolder
R3: 10k; R_0603_1608Metric_Pad0.98x0.95mm_HandSolder
R4: 5.1K; R_0603_1608Metric_Pad0.98x0.95mm_HandSolder
R5: 100; R_0603_1608Metric_Pad0.98x0.95mm_HandSolder
T1: ZMPT101B; XFMR_ZMPT101B
U1: DFR0654; MODULE_DFR0654
U2: MT3608_DC-DC_STEP_UP_CONVERTER_2A_BOOSTER_MODULE; MODULE_MT3608_DC-DC_STEP_UP_CONVERTER_2A_BOOSTER_MODULE

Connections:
3.3V: U1.2 (3.3V), U1.31 (3.3V)
/2v-28v: J2.2, U2.VOUT_P (VOUT+)
/5v: C2.2, J2.4, J3.4, PS1.4 (+VO), R3.2, U1.32 (VCC), U2.VIN_P (VIN+)
/L: F1.2, J1.1
/N: J1.2, PS1.1 (AC1), T1.1
/ZMPT101B: C1.2, J2.3, J3.3, R3.1, R4.2, R5.2
GND: C2.1, C3.2, J2.1, J3.1, PS1.3 (-VO), R2.1, R4.1, T1.4, U1.4 (GND), U1.30 (GND), U2.VIN_N (VIN-), U2.VOUT_N (VOUT-)
unnamed: C1.1, R2.2, T1.3
unnamed: F1.1, PS1.2 (AC2), R1.1
unnamed: R1.2, T1.2
unnamed: C3.1, R5.1, U1.26 (A3)

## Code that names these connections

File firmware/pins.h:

/*
 * GridWatcher v0.3 PCB pin definitions (ESP32-S3-WROOM-1-N16R8, U6)
 * Matched to Hardware/GridWatcher_v0.3/GriDwatcher china.kicad_pcb
 */

#ifndef PINS_H
#define PINS_H

// BL0939 energy metering IC (U2)
#define PIN_BL0939_RX          1   // U6 IO1 <- U2 pad 15 (TX/SDO)
#define PIN_BL0939_TX          2   // U6 IO2 -> U2 pad 14 (RX/SDI)
#define PIN_BL0939_ZX          3   // U6 IO3 <- U2 pad 9 (ZX zero-crossing output)

// BQ24074 charger/power-path (U3) & MAX17048 fuel gauge (U5)
#define PIN_BQ24074_CHG        4   // ~CHG open-drain (LOW = charging)
#define PIN_BQ24074_PGOOD      5   // ~PGOOD open-drain (LOW = AC mains present, HIGH = mains lost)
#define PIN_I2C_SDA            6   // MAX17048 SDA
#define PIN_I2C_SCL            7   // MAX17048 SCL
#define PIN_MAX17048_ALERT     8   // MAX17048 ~ALERT

// XTSDG08GWSIGA 1GB SD-NAND flash (U7, 1-bit SDMMC)
#define PIN_SDNAND_CMD        11
#define PIN_SDNAND_CLK        12   // routed through R22 (22 ohm)
#define PIN_SDNAND_DAT0       13
#define PIN_SDNAND_CS         14   // DAT3/CS (net labeled /IO10 on schematic)

// SIMCom A7670E LTE Cat-1 modem (via TXS0102 level shifter & BSS138 FETs)
#define PIN_MODEM_RESET       15   // Q2 gate
#define PIN_MODEM_PWRKEY      16   // Q1 gate
#define PIN_MODEM_TX_3V3      17   // ESP32 TX -> TXS0102 -> Modem RXD
#define PIN_MODEM_RX_3V3      18   // ESP32 RX <- TXS0102 <- Modem TXD

#endif // PINS_H

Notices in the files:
parts and their libraries:
XTX SD NAND LGA-8 with exposed pad, 6x8mm body, 1.27mm pitch (XTSDG08GWSIGA / XTSDG04GWSIGA). MIT (c) 2026 Kyle Richter
License: MIT (c) 2026 Kyle Richter
